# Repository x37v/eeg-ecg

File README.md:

# DIY EEG/ECG

Layout of circuit from [DIY EEG and ECG instructable](http://www.instructables.com/id/DIY-EEG-and-ECG-Circuit/).
I added a power header and some decoupling caps.

Schematic/PCB use KiCad.

[oshpark project](https://oshpark.com/projects/CZ6dmHz6) untested so far.

## BOM

### Caps

* 5 **220n**                     C1,C3,C4,C5,C8
* 7 **100n**                     C6,C12,C13,C14,C15,C18,C19
* 1 **25n**                      C7
* 1 **10n**                      C11
* 4 **10u**                      C2,C9,C16,C17 *electrolytic*
* 1 **1u**                       C10 *electrolytic*

### Resistors:

* 1 **560R**                     R1
* 2 **22k**                      R2,R10
* 2 **12R**                      R3,R11
* 2 **220R**                     R4,R14
* 1 **47k**                      R5
* 1 **220K**                     R6
* 2 **180k**                     R7,R8
* 2 **100k**                     R9,R15
* 1 **200R**                     R12
* 1 **1M**                       R13

### Semi:

* 1 [**AD620AN**](http://www.digikey.com/product-detail/en/AD620ANZ/AD620ANZ-ND/750967)                    U1
* 1 **TL072**                    U2
* 1 **TL074**                    U3

*note* original project used 2x 084 op amps.. you can use 08x series in place of these..

### Other:

* 1 **1k POT**                   P4
* 2 **bead**                     R16,R17  *optional*

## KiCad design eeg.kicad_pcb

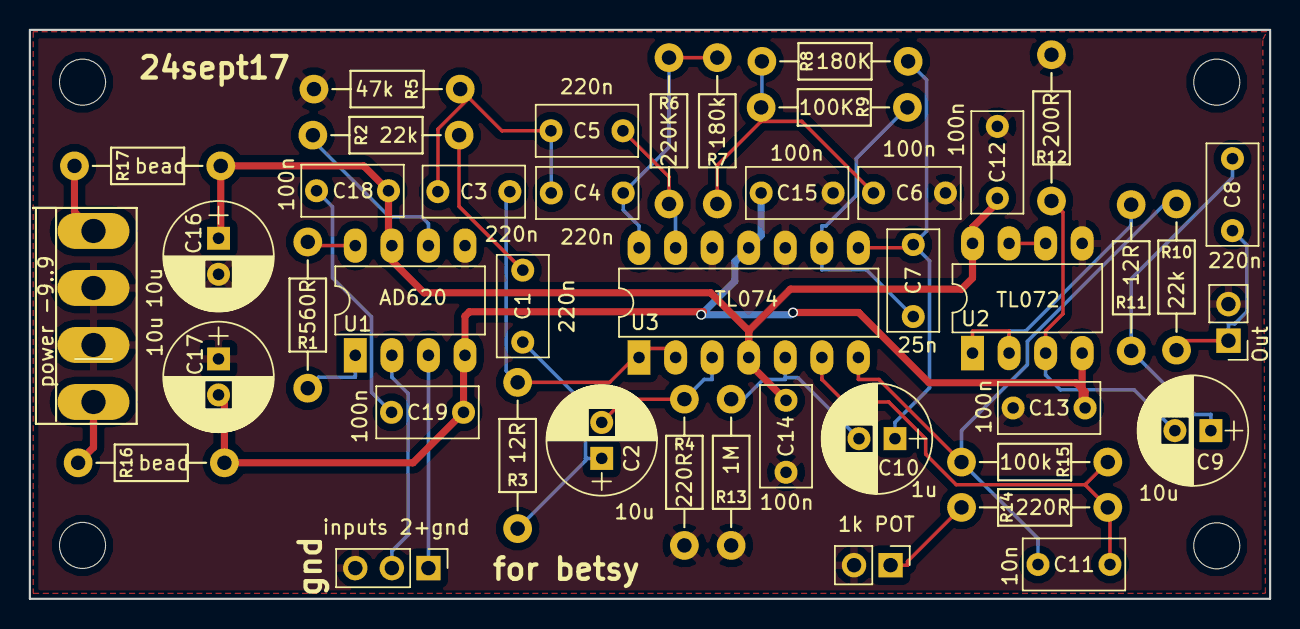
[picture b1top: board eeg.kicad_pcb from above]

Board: 2 copper layers, 86.2 x 39.5 mm, 47 parts (0 on the bottom side), 30 nets.

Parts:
C1, C3, C4, C5, C8: 220n; C_Rect_L7.0mm_W3.5mm_P5.00mm
C2, C9, C16, C17: 10u; CP_Radial_D7.5mm_P2.50mm
C6, C12, C13, C14, C15, C18, C19: 100n; C_Rect_L7.0mm_W3.5mm_P5.00mm
C7: 25n; C_Rect_L7.0mm_W3.5mm_P5.00mm
C10: 1u; CP_Radial_D7.5mm_P2.50mm
C11: 10n; C_Rect_L7.0mm_W3.5mm_P5.00mm
P1: inputs 2+gnd; Pin_Header_Straight_1x03_Pitch2.54mm
P2: power -9..9; MTA-156-4
P3: Out; Pin_Header_Straight_1x02_Pitch2.54mm
P4: 1k POT; Pin_Header_Straight_1x02_Pitch2.54mm
R1: 560R; Resistor_Horizontal_RM10mm-xnorman
R2, R10: 22k; Resistor_Horizontal_RM10mm-xnorman
R3, R11: 12R; Resistor_Horizontal_RM10mm-xnorman
R4, R14: 220R; Resistor_Horizontal_RM10mm-xnorman
R5: 47k; Resistor_Horizontal_RM10mm-xnorman
R6: 220K; Resistor_Horizontal_RM10mm-xnorman
R7: 180k; Resistor_Horizontal_RM10mm-xnorman
R8: 180K; Resistor_Horizontal_RM10mm-xnorman
R9: 100K; Resistor_Horizontal_RM10mm-xnorman
R12: 200R; Resistor_Horizontal_RM10mm-xnorman
R13: 1M; Resistor_Horizontal_RM10mm-xnorman
R15: 100k; Resistor_Horizontal_RM10mm-xnorman
R16, R17: bead; Resistor_Horizontal_RM10mm-xnorman
REF1, REF2, REF3, REF4: MountingHole_3.2mm_M3
U1: AD620; DIP-8_W7.62mm_LongPads
U2: TL072; DIP-8_W7.62mm_LongPads
U3: TL074; DIP-14_W7.62mm_LongPads

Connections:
GND: C6.1, C12.1, C13.2, C14.1, C15.2, C16.2, C17.1, P1.3, P2.2, P2.3, P3.2, P4.2, R4.1, R5.1, R12.1, R13.2, U1.5, U2.5, U3.10, U3.12
unnamed: C1.1, C2.1, R3.2
unnamed: C1.2, R2.1
unnamed: C2.2, R4.2, U3.3
unnamed: C3.1, C4.1, C5.2, R5.2
unnamed: C3.2, R3.1, U3.1, U3.2
unnamed: C4.2, R6.2, R7.1, U3.14
unnamed: C5.1, R6.1, U3.13
unnamed: C6.2, R7.2, R8.2, R9.1
unnamed: C7.1, R9.2, U3.9
unnamed: C8.1, P3.1, R10.1
unnamed: C8.2, C9.1, R11.2
unnamed: C9.2, R12.2, U2.3
unnamed: C7.2, C10.1, R8.1, U3.8
unnamed: C10.2, R13.1, U3.5
unnamed: C11.1, R14.1, R15.2, U3.6
unnamed: C11.2, R10.2, R15.1, U3.7
unnamed: C18.1, C19.2
unnamed: P1.1, U1.3
unnamed: P1.2, U1.2
unnamed: P2.1, R17.2
unnamed: P2.4, R16.2
unnamed: P4.1, R14.2
unnamed: R1.1, U1.8
unnamed: R1.2, U1.1
unnamed: R2.2, U1.6
unnamed: R11.1, U2.1, U2.2
unnamed: U2.6, U2.7
VCC: C12.2, C14.2, C16.1, C18.2, R17.1, U1.7, U2.8, U3.4
VEE: C13.1, C15.1, C17.2, C19.1, R16.1, U1.4, U2.4, U3.11

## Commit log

2017-09-24 initial layout
2017-09-24 added BOM
2017-09-24 added link
